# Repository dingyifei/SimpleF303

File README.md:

# SimpleF303
 A QFP-48 STM32F303 minimum board design

## Features:

1. It is functional
2. u can replace the LDO with a more powerful one
3. hand solder
4. Simple?

## Known Issues:

- it doesn't have LED indicator 
- you need to pull BOOT0 to 3.3v before pulling the NRST pin in order to enter DFU
- Uncommon reset button footprint (you can easily replace it )
- Maybe impossible to power it without USB
- hard to solder SMD crystal (you can easily replace it )

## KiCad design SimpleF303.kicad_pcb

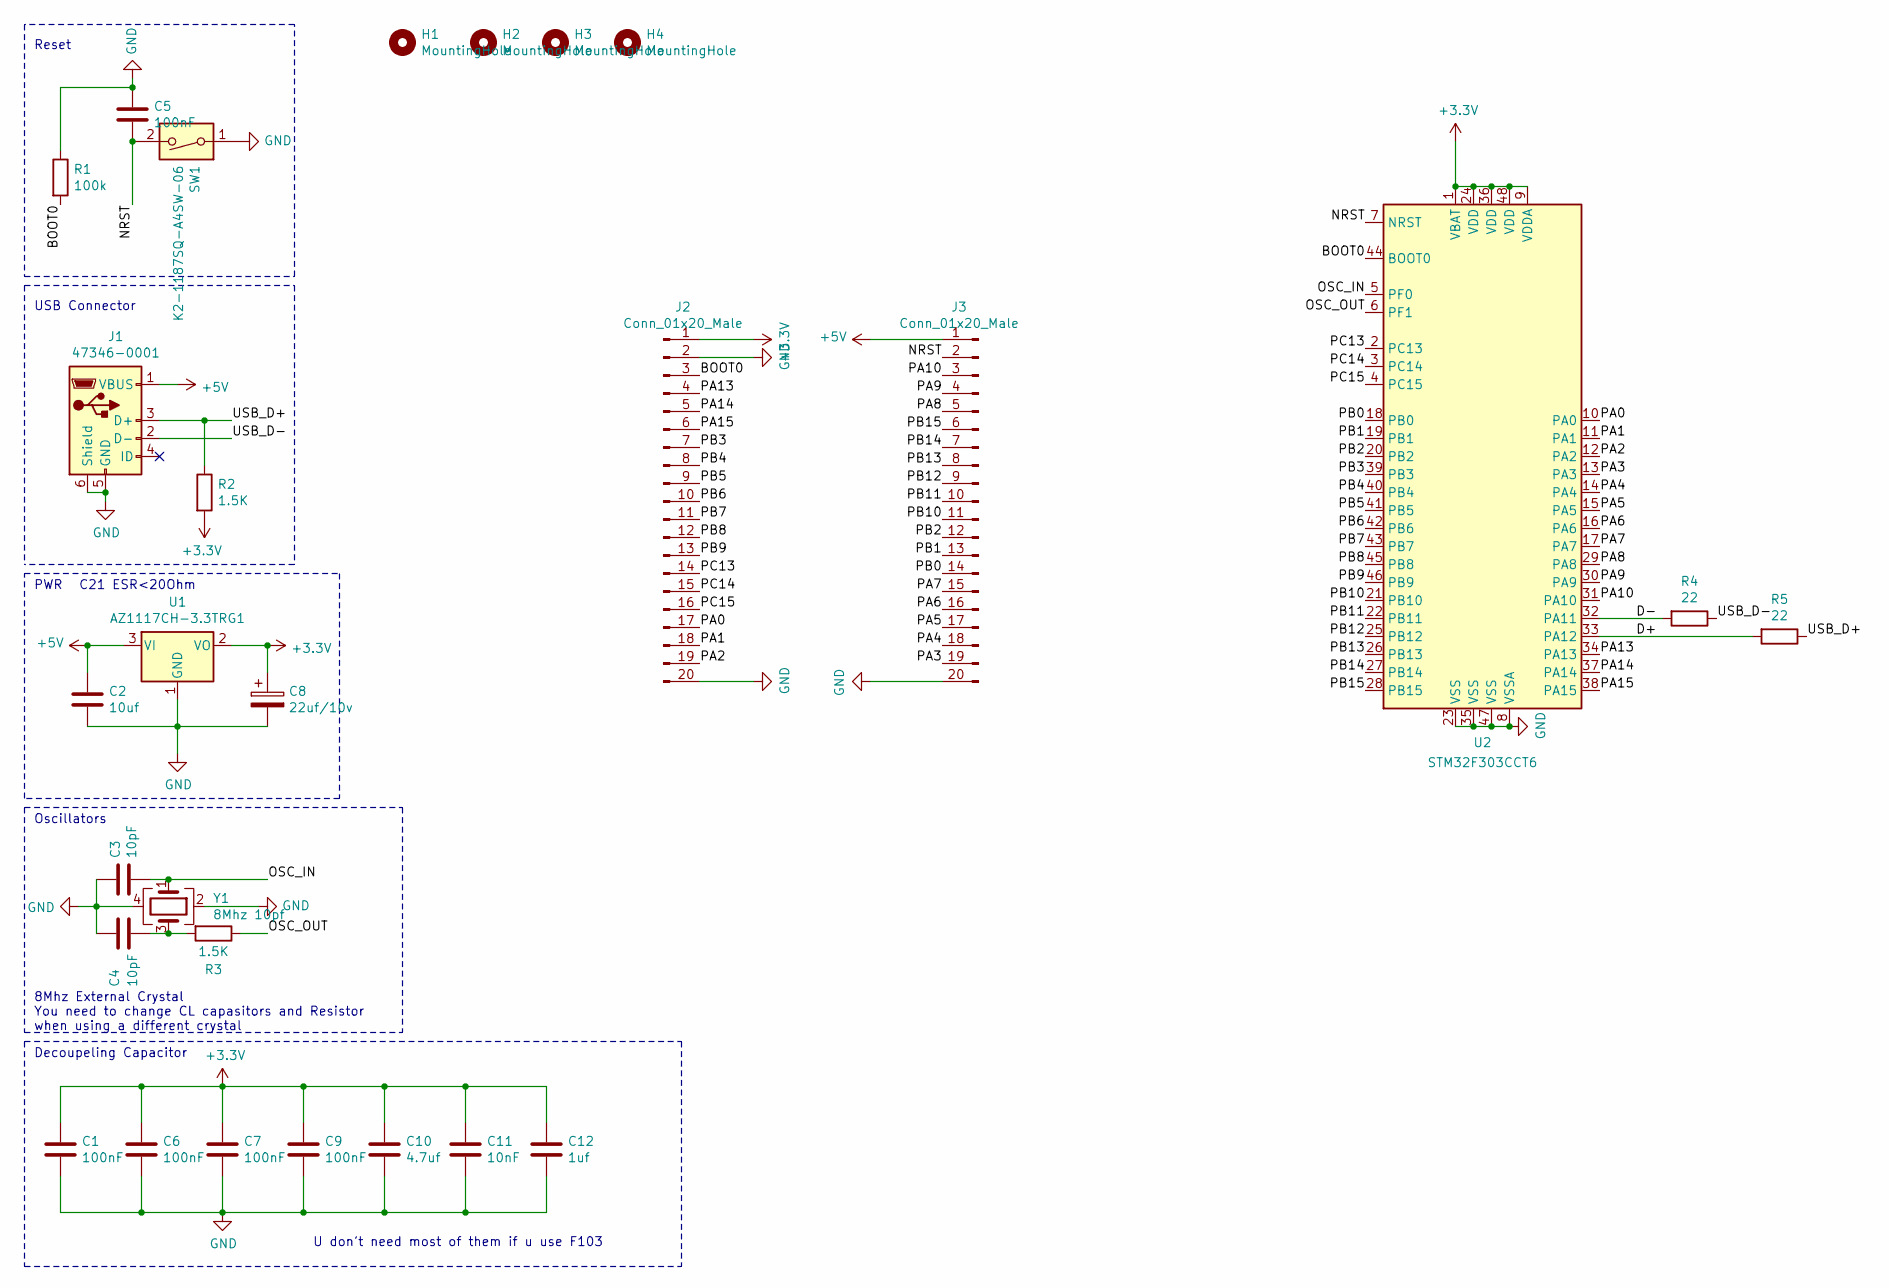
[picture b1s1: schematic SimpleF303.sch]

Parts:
C1, C5, C6, C7, C9: 100nF; C_0603_1608Metric; Part Number 0603B104K160CT; LCSC C80516
C2: 10uf; C_0603_1608Metric; Part Number 0603X106K100NT; LCSC C38898
C3, C4: 10pF; C_0603_1608Metric; Part Number CC0603GRNPO9BN100; LCSC C325468
C8: 22uf/10v; CP_EIA-3216-18_Kemet-A; Part Number TAJA226K010RNJ; LCSC C11366
C10: 4.7uf; C_0603_1608Metric; Part Number CL10A475KA8NQNC; LCSC C69335
C11: 10nF; C_0603_1608Metric; Part Number CL10B103JB8NNNC; LCSC C7248
C12: 1uf; C_0603_1608Metric; Part Number UMK107AB7105KA-T; LCSC C105174
H1, H2, H3, H4: MountingHole; MountingHole_2.1mm
J1: 47346-0001; USB_Micro-B_Molex_47346-0001; Part Number 47346-0001; LCSC C132560
J2, J3: Conn_01x20_Male; PinHeader_1x20_P2.54mm_Vertical; Part Number 2.54mm 1x40P; LCSC C2337
R1: 100k; R_0603_1608Metric; Part Number CR0603FA1003G; LCSC C100703
R2, R3: 1.5K; R_0603_1608Metric; Part Number RTT031501FTP; LCSC C103303
R4, R5: 22; R_0603_1608Metric; Part Number CR0603FA22R0G; LCSC C100876
SW1: K2-1187SQ-A4SW-06; Part Number K2-1187SQ-A4SW-06; LCSC C92584
U1: AZ1117CH-3.3TRG1; SOT-223-3_TabPin2; Part Number AZ1117CH-3.3TRG1; LCSC C92102
U2: STM32F303CCT6; LQFP-48_7x7mm_P0.5mm; Part Number STM32F303CCT6; LCSC C81523
Y1: 8Mhz 10pf; Crystal_SMD_3225-4Pin_3.2x2.5mm; Part Number TAXM8M4RDBCCT2T; LCSC C400090

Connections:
+3V3: C1.1, C6.1, C7.1, C8.1, C9.1, C10.1, C11.1, C12.1, J2.1, R2.2, U1.2 (VO), U2.1 (VBAT), U2.9 (VDDA), U2.24 (VDD), U2.36 (VDD), U2.48 (VDD)
+5V: C2.1, J1.1 (VBUS), J3.1, U1.3 (VI)
/BOOT0: J2.3, R1.2, U2.44 (BOOT0)
/D+: R5.2, U2.33 (PA12)
/D-: R4.2, U2.32 (PA11)
/NRST: C5.2, J3.2, SW1.2, U2.7 (NRST)
/OSC_IN: C3.2, U2.5 (PF0), Y1.1
/OSC_OUT: R3.1, U2.6 (PF1)
/PA0: J2.17, U2.10 (PA0)
/PA1: J2.18, U2.11 (PA1)
/PA2: J2.19, U2.12 (PA2)
/PA3: J3.19, U2.13 (PA3)
/PA4: J3.18, U2.14 (PA4)
/PA5: J3.17, U2.15 (PA5)
/PA6: J3.16, U2.16 (PA6)
/PA7: J3.15, U2.17 (PA7)
/PA8: J3.5, U2.29 (PA8)
/PA9: J3.4, U2.30 (PA9)
/PA10: J3.3, U2.31 (PA10)
/PA13: J2.4, U2.34 (PA13)
/PA14: J2.5, U2.37 (PA14)
/PA15: J2.6, U2.38 (PA15)
/PB0: J3.14, U2.18 (PB0)
/PB1: J3.13, U2.19 (PB1)
/PB2: J3.12, U2.20 (PB2)
/PB3: J2.7, U2.39 (PB3)
/PB4: J2.8, U2.40 (PB4)
/PB5: J2.9, U2.41 (PB5)
/PB6: J2.10, U2.42 (PB6)
/PB7: J2.11, U2.43 (PB7)
/PB8: J2.12, U2.45 (PB8)
/PB9: J2.13, U2.46 (PB9)
/PB10: J3.11, U2.21 (PB10)
/PB11: J3.10, U2.22 (PB11)
/PB12: J3.9, U2.25 (PB12)
/PB13: J3.8, U2.26 (PB13)
/PB14: J3.7, U2.27 (PB14)
/PB15: J3.6, U2.28 (PB15)
/PC13: J2.14, U2.2 (PC13)
/PC14: J2.15, U2.3 (PC14)
/PC15: J2.16, U2.4 (PC15)
/USB_D+: J1.3 (D+), R2.1, R5.1
/USB_D-: J1.2 (D-), R4.1
GND: C1.2, C2.2, C3.1, C4.1, C5.1, C6.2, C7.2, C8.2, C9.2, C10.2, C11.2, C12.2, J1.5 (GND), J1.6 (Shield), J2.2, J2.20, J3.20, R1.1, SW1.1, U1.1 (GND), U2.8 (VSSA), U2.23 (VSS), U2.35 (VSS), U2.47 (VSS), Y1.2, Y1.4
unnamed: C4.2, R3.2, Y1.3

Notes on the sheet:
PWR
C21 ESR<20Ohm
8Mhz External Crystal You need to change CL capasitors and Resistor when using a different crystal
USB Connector
Oscillators
Decoupeling Capacitor
Reset
U don't need most of them if u use F103

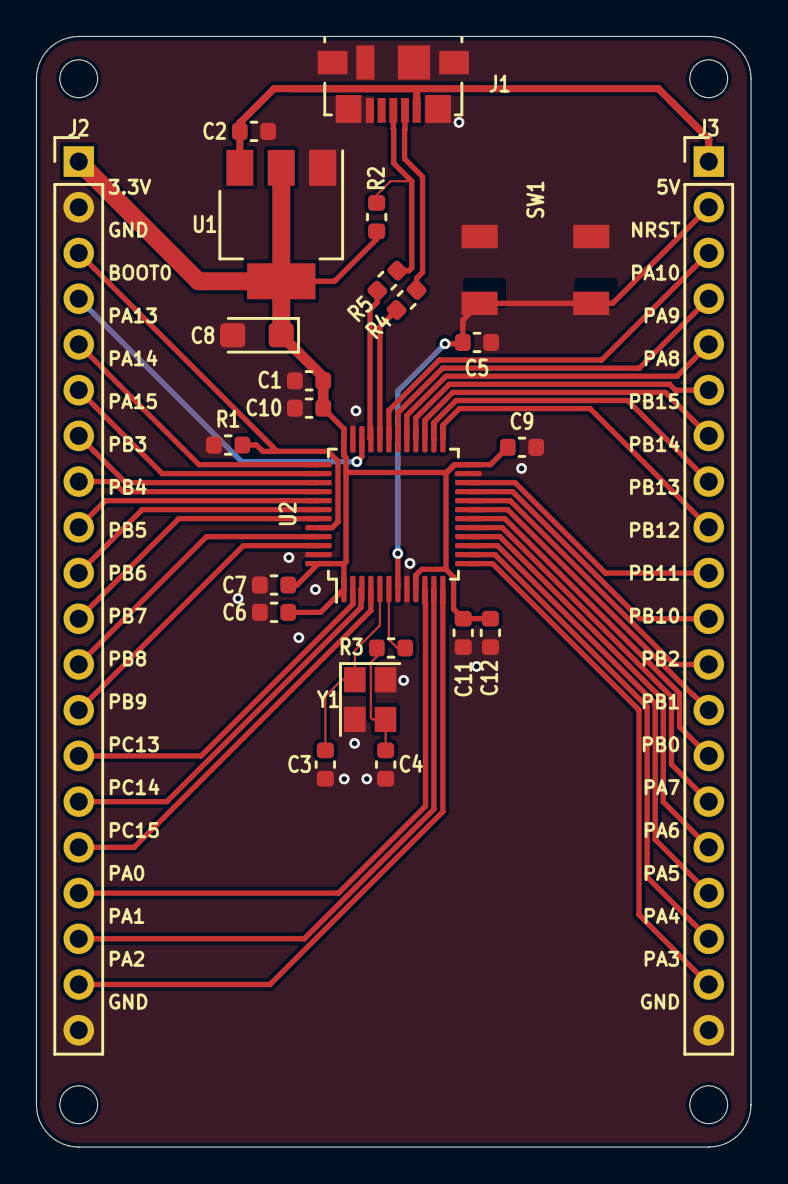
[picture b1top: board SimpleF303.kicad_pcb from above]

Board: 2 copper layers, 39.7 x 61.7 mm, 28 parts (0 on the bottom side), 45 nets.

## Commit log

2020-02-15 I think it will work
2020-02-17 clearly I can't get some parts so I change selection
2020-02-20 small changes
2020-02-21 Appearently buy parts is hard
2020-03-27 update pcb, add BOM, edit readme

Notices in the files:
SimpleF303.kicad_pcb:
MIT License Copyright (c) 2019 Yifei Ding
